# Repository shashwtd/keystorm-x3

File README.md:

## Keystorm X3

A controller board with 3 LEDs, 3 Cherry MX Switches, and a Buzzer that can be used as a macropad. images below display the board 3d renders, pcb design & the schematic design

The core idea of this macropad is to allow mode switching by long pressing the 3 buttons. This macropad can either be used as a copy paste enter shortcut, your music player control, or your discord voice chat mute/unmute/deafen controller. The buzzer helps with sound feedback so you know when a button is pressed or an action happens. It has a nice startup animation with lights + buzzers which plays when the board boots up.

The BOM can be found [here](https://docs.google.com/spreadsheets/d/1Z7pQt6PCEZvinR357QXdnwnkV8Bckr60LjoRv5xW0wc/edit?usp=sharing)

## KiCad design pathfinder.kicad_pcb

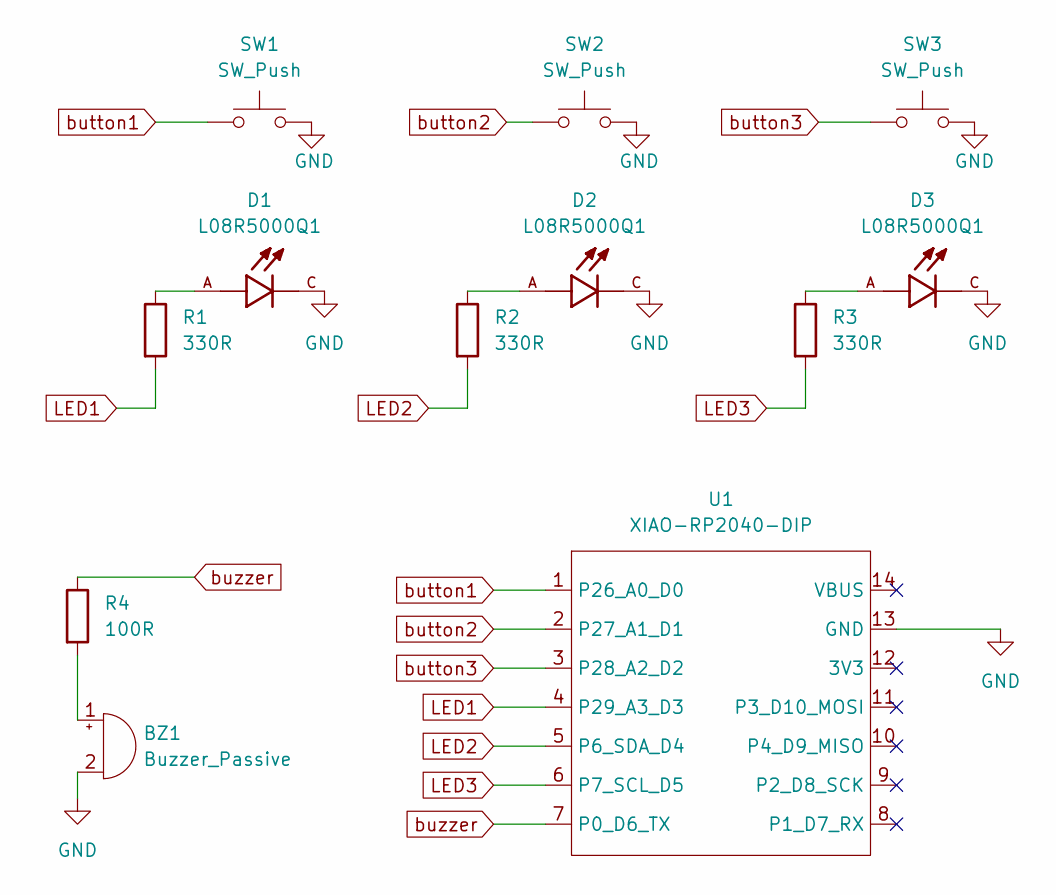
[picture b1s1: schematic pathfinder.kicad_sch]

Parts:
BZ1: Buzzer_Passive; Buzzer_12x9.5RM7.6
D1, D2, D3: L08R5000Q1; LEDRD254W57D500H1070; PARTREV NA
R1, R2, R3: 330R; R_Axial_DIN0411_L9.9mm_D3.6mm_P12.70mm_Horizontal
R4: 100R; R_Axial_DIN0411_L9.9mm_D3.6mm_P12.70mm_Horizontal
SW1, SW2, SW3: SW_Push; SW_Cherry_MX_1.00u_PCB
U1: XIAO-RP2040-DIP

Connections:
GND: BZ1.2 (-), D1.C, D2.C, D3.C, SW1.2, SW2.2, SW3.2, U1.13 (GND)
LED1: R1.2, U1.4 (P29_A3_D3)
LED2: R2.2, U1.5 (P6_SDA_D4)
LED3: R3.2, U1.6 (P7_SCL_D5)
unnamed: BZ1.1 (+), R4.2
unnamed: D1.A, R1.1
unnamed: D2.A, R2.1
unnamed: D3.A, R3.1
button1: SW1.1, U1.1 (P26_A0_D0)
button2: SW2.1, U1.2 (P27_A1_D1)
button3: SW3.1, U1.3 (P28_A2_D2)
buzzer: R4.1, U1.7 (P0_D6_TX)

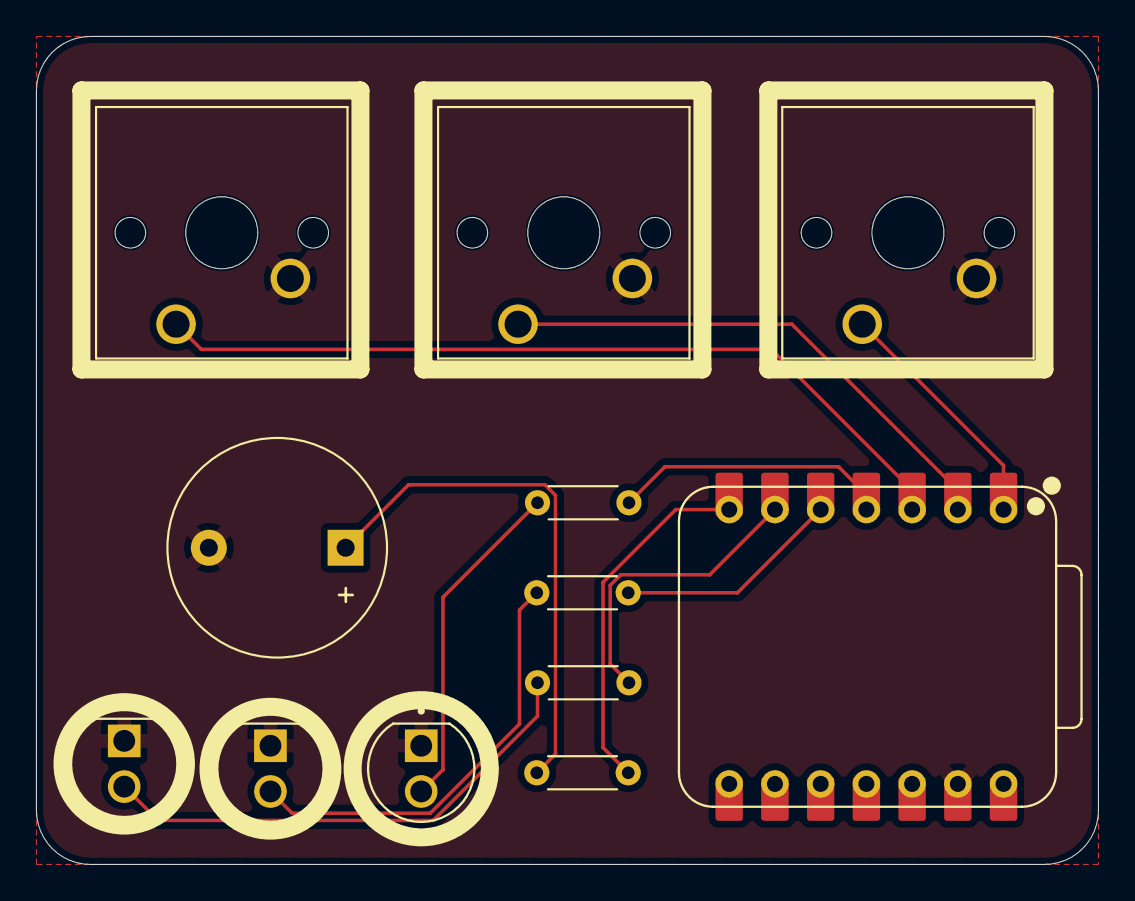
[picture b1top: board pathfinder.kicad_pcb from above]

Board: 2 copper layers, 59.0 x 46.0 mm, 12 parts (0 on the bottom side), 12 nets.

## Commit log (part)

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2026-05-22 schematic designs complete
2026-05-22 dump
2026-05-22 organized it all
2026-05-24 installing a buzer in the schematic desgin
2026-05-24 mapped footprints & added all the 3d files
2026-05-24 pcb design done
2026-05-24 added 3d models for buttons
2026-05-24 added board & led light 3 d models
2026-05-24 doing silkboard designs
2026-05-24 more silkscreen designs cuz why not
2026-05-24 wrote a firmware script for the board to act as a mini keeb
2026-05-25 added a BOM, done some final changes & added a README file
2026-05-25 added a BOM.csv
2026-05-25 fix image naming & convert md image format to github instead of obsidian
2026-06-01 fix images inline & add time spent details for better practice
